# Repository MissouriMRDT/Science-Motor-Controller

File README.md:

# ScienceMotorController_Hardware
Hardware files for the Science Motor Controller (Science MOCO) board <br/>
The entire science system runs off of the 12V 40A auxillary buck from Powerboard. 
Science MOCO disctributes power to the rest of the science system (heater board and science sensors) in addition to driving brushed DC motors, servos, and solenoids.

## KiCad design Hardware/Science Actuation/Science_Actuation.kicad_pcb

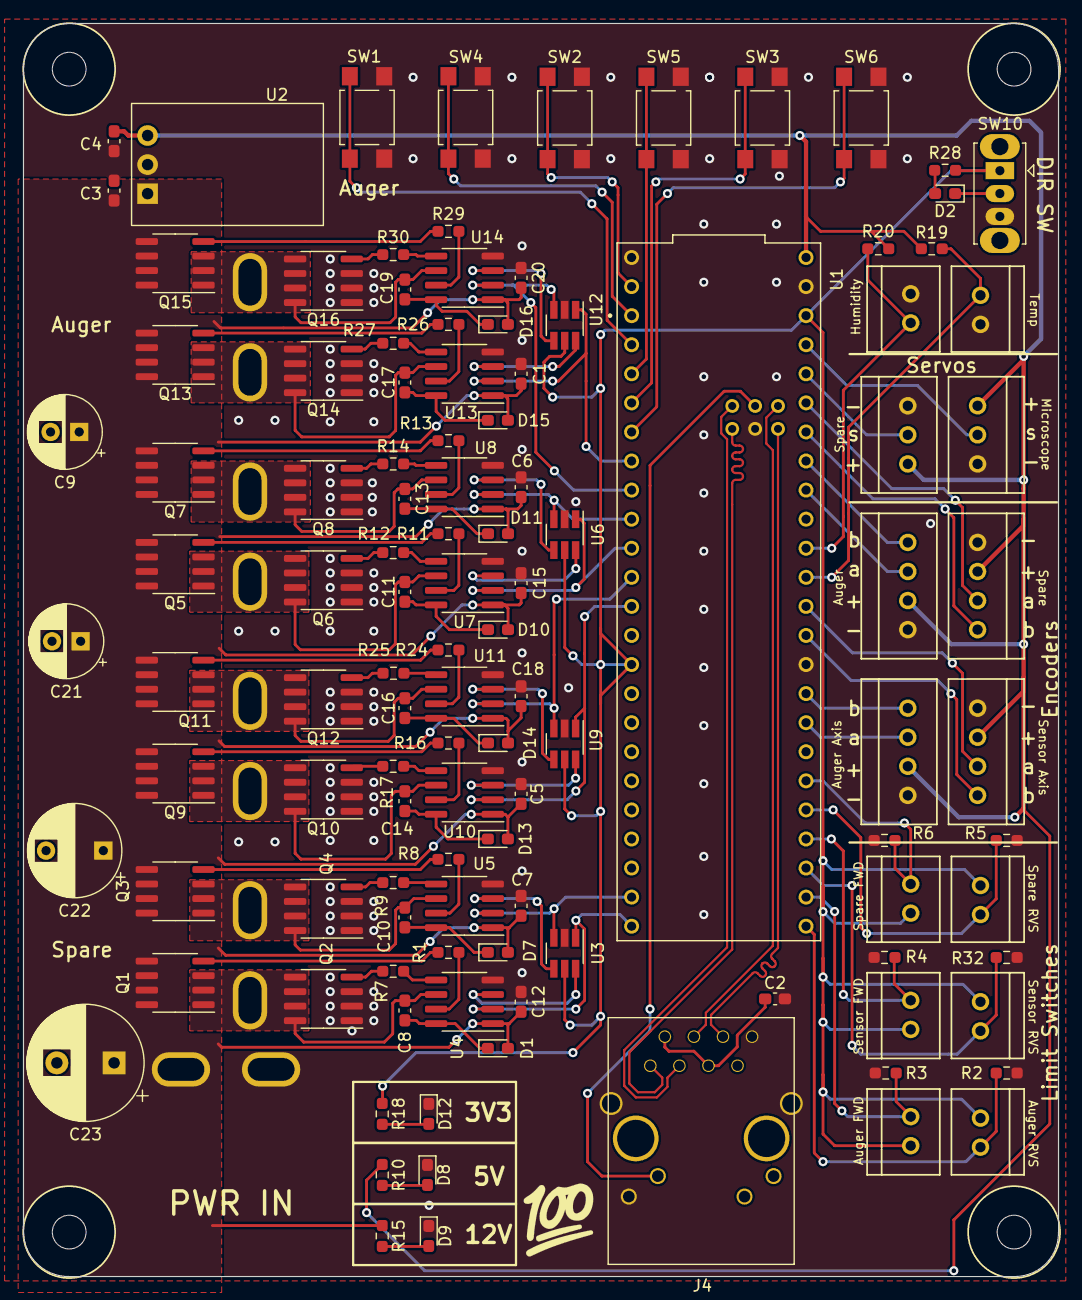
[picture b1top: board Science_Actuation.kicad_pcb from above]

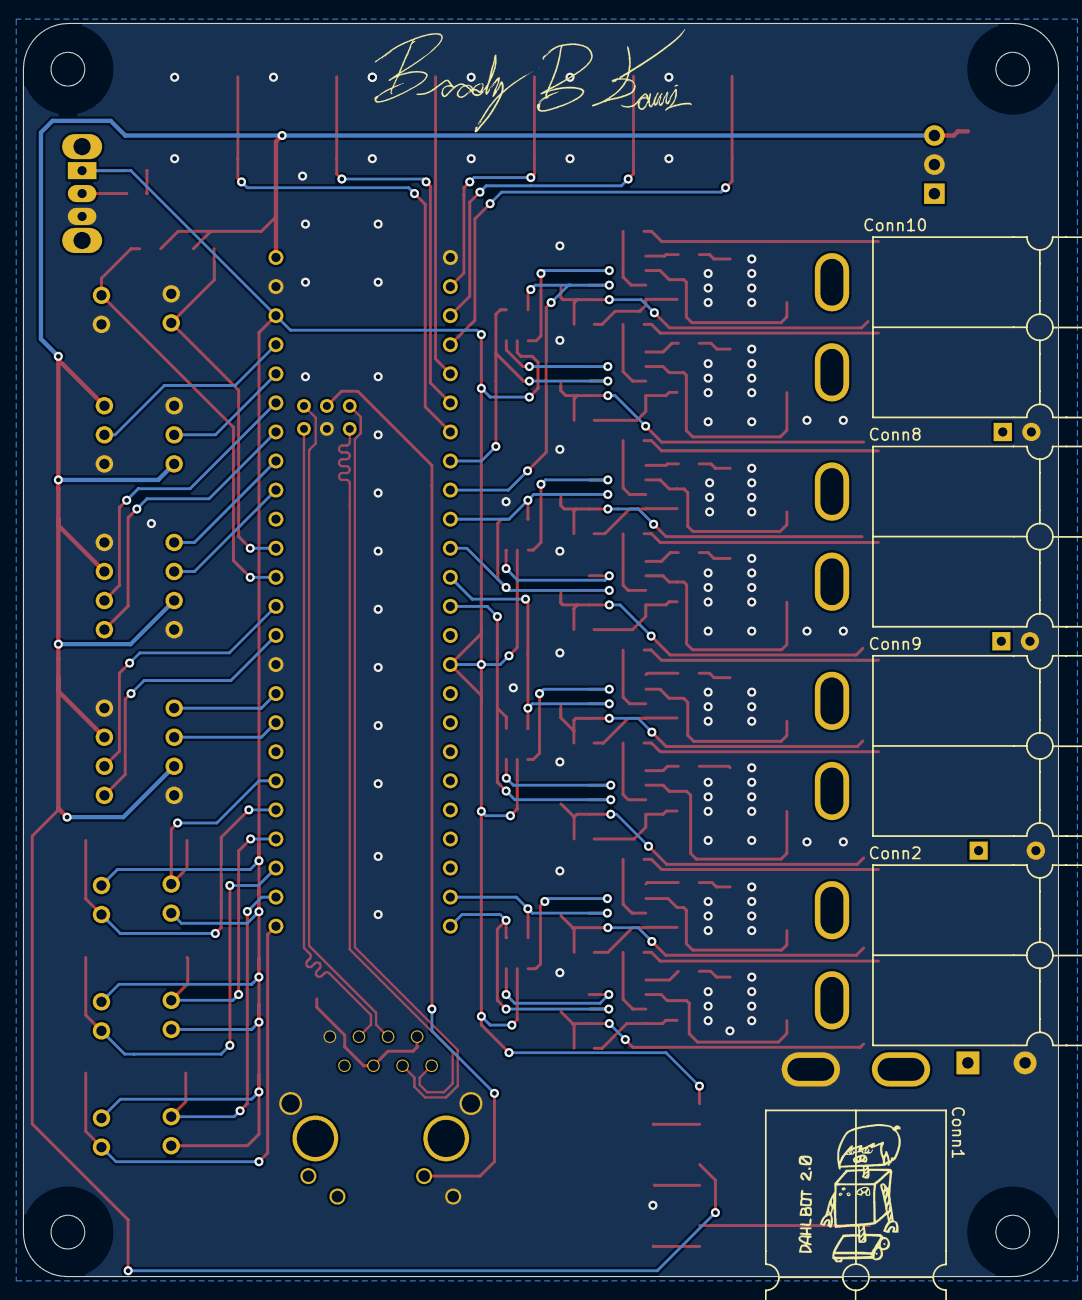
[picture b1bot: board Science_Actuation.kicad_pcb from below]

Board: 2 copper layers, 90.4 x 109.5 mm, 124 parts (5 on the bottom side), 103 nets.

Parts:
C1, C3, C4, C5, C6, C7, C12, C15, C18, C20: 10uF; C_0603_1608Metric_Pad1.08x0.95mm_HandSolder
C2: 0.1uF; C_0603_1608Metric_Pad1.08x0.95mm_HandSolder
C8, C10, C11, C13, C14, C16, C17, C19: 1uF; C_0603_1608Metric_Pad1.08x0.95mm_HandSolder
C9: 100uF; CP_Radial_D6.3mm_P2.50mm
C21: 220uF; CP_Radial_D6.3mm_P2.50mm
C22: 330uF; CP_Radial_D8.0mm_P5.00mm
C23: 470uF; CP_Radial_D10.0mm_P5.00mm
Conn1, Conn2, Conn8, Conn9, Conn10: AndersonPP; Square_Anderson_2_H_Side_By_Side
Conn3, Conn4, Conn5, Conn6, Conn7, Conn11, Conn12, Conn13: Molex_SL_02; MOLEX_SL_02_Vertical
D1, D7, D10, D11, D13, D14, D15, D16: SD0603S04; D_0603_1608Metric_Pad1.05x0.95mm_HandSolder
D2: Blue; LED_0603_1608Metric_Pad1.05x0.95mm_HandSolder
D8, D9, D12: Green; LED_0603_1608Metric_Pad1.05x0.95mm_HandSolder
H1, H2, H3, H4: MountingHole; 4_40_Hole_Corner
J4: RJ45_LED_Shielded; RJ45_Teensy
Q1, Q2, Q3, Q4, Q5, Q6, Q7, Q8, Q9, Q10, Q11, Q12, Q13, Q14, Q15, Q16: Si4156DY; SOIC-8_3.9x4.9mm_P1.27mm
QuadEncode1, QuadEncode2, QuadEncode3, QuadEncode4: Molex_SL_04; MOLEX_SL_04_Vertical
R1, R7, R8, R9, R11, R12, R13, R14, R16, R17, R24, R25, R26, R27, R29, R30: 100; R_0603_1608Metric_Pad0.98x0.95mm_HandSolder
R2, R3, R4, R5, R6, R32: 4700; R_0603_1608Metric_Pad0.98x0.95mm_HandSolder
R10: 560; R_0603_1608Metric_Pad0.98x0.95mm_HandSolder
R15: 2.2k; R_0603_1608Metric_Pad0.98x0.95mm_HandSolder
R18: 300; R_0603_1608Metric_Pad0.98x0.95mm_HandSolder
R19: 25; R_0603_1608Metric_Pad0.98x0.95mm_HandSolder
R20: 50k; R_0603_1608Metric_Pad0.98x0.95mm_HandSolder
R28: 30; R_0603_1608Metric_Pad0.98x0.95mm_HandSolder
SW1, SW2, SW3, SW4, SW5, SW6: SW_Push; SW_SPST_TL3305A
SW10: SW_SPDT; SW_Slide_1P2T_CK_OS102011MS2Q
Servo1, Servo2: Molex_SL_03; MOLEX_SL_03_Vertical
U1: Teensy4.1_DEV-16771; Teensy_4_1_Ethernet
U2: OKI-78SR-5_1.5-W36H-C; Converter_DCDC_Murata_OKI-78SR_Horizontal
U3, U6, U9, U12: 74LVC2G04; SOT-23-6_Handsoldering
U4, U5, U7, U8, U10, U11, U13, U14: IRS2308; SOIC-8_3.9x4.9mm_P1.27mm

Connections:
+3V3: Conn3.1, Conn4.1, Conn5.1, Conn6.1, Conn7.1, Conn11.1, R18.1, R28.1, SW10.1 (A), U1.3.3V_1 (3.3V), U1.3.3V_2 (3.3V), U3.5 (VCC), U6.5 (VCC), U9.5 (VCC), U12.5 (VCC)
+5V: C4.1, QuadEncode1.2, QuadEncode2.2, QuadEncode3.2, QuadEncode4.2, R10.1, R19.1, R20.1, Servo1.1, Servo2.1, U1.VIN, U2.3 (OUT)
+12V: C1.1, C3.1, C5.1, C6.1, C7.1, C9.1, C12.1, C15.1, C18.1, C20.1, C21.1, C22.1, C23.1, Conn1.2 (V+Log), D1.2 (A), D7.2 (A), D10.2 (A), D11.2 (A), D13.2 (A), D14.2 (A), D15.2 (A), D16.2 (A), Q1.5 (D), Q1.6 (D), Q1.7 (D), Q1.8 (D), Q3.5 (D), Q3.6 (D), Q3.7 (D), Q3.8 (D), Q5.5 (D), Q5.6 (D), Q5.7 (D), Q5.8 (D), Q7.5 (D), Q7.6 (D), Q7.7 (D), Q7.8 (D), Q9.5 (D), Q9.6 (D), Q9.7 (D), Q9.8 (D), Q11.5 (D), Q11.6 (D), Q11.7 (D), Q11.8 (D), Q13.5 (D), Q13.6 (D), Q13.7 (D), Q13.8 (D), Q15.5 (D), Q15.6 (D), Q15.7 (D), Q15.8 (D), R15.1, U2.1 (IN), U4.1 (VCC), U5.1 (VCC), U7.1 (VCC), U8.1 (VCC), U10.1 (VCC), U11.1 (VCC), U13.1 (VCC), U14.1 (VCC)
/M1+: C8.2, Conn2.1 (GND), Q1.1 (S), Q1.2 (S), Q1.3 (S), Q2.5 (D), Q2.6 (D), Q2.7 (D), Q2.8 (D), U4.6 (VS)
/M1-: C10.2, Conn2.2 (V+Log), Q3.1 (S), Q3.2 (S), Q3.3 (S), Q4.5 (D), Q4.6 (D), Q4.7 (D), Q4.8 (D), U5.6 (VS)
/M2+: C11.2, Conn8.1 (GND), Q5.1 (S), Q5.2 (S), Q5.3 (S), Q6.5 (D), Q6.6 (D), Q6.7 (D), Q6.8 (D), U7.6 (VS)
/M2-: C13.2, Conn8.2 (V+Log), Q7.1 (S), Q7.2 (S), Q7.3 (S), Q8.5 (D), Q8.6 (D), Q8.7 (D), Q8.8 (D), U8.6 (VS)
/M3+: C14.2, Conn9.1 (GND), Q9.1 (S), Q9.2 (S), Q9.3 (S), Q10.5 (D), Q10.6 (D), Q10.7 (D), Q10.8 (D), U10.6 (VS)
/M3-: C16.2, Conn9.2 (V+Log), Q11.1 (S), Q11.2 (S), Q11.3 (S), Q12.5 (D), Q12.6 (D), Q12.7 (D), Q12.8 (D), U11.6 (VS)
/M4+: C17.2, Conn10.1 (GND), Q13.1 (S), Q13.2 (S), Q13.3 (S), Q14.5 (D), Q14.6 (D), Q14.7 (D), Q14.8 (D), U13.6 (VS)
/M4-: C19.2, Conn10.2 (V+Log), Q15.1 (S), Q15.2 (S), Q15.3 (S), Q16.5 (D), Q16.6 (D), Q16.7 (D), Q16.8 (D), U14.6 (VS)
DIR_SW: D2.1 (K), SW10.2 (B)
Encoder_1a: QuadEncode4.3, U1.40 (A16)
Encoder_1b: QuadEncode4.4, U1.41 (A17)
Encoder_2a: QuadEncode1.3, U1.18 (A4)
Encoder_2b: QuadEncode1.4, U1.19 (A5)
Encoder_3a: QuadEncode2.3, U1.21 (A7)
Encoder_3b: QuadEncode2.4, U1.20 (A6)
Encoder_4a: QuadEncode3.3, U1.14 (A0)
Encoder_4b: QuadEncode3.4, U1.13 (SCK)
GND: C1.2, C2.1, C3.2, C4.2, C5.2, C6.2, C7.2, C9.2, C12.2, C15.2, C18.2, C20.2, C21.2, C22.2, C23.2, Conn1.1 (GND), Conn12.2, Conn13.2, D8.1 (K), D9.1 (K), D12.1 (K), J4.8, J4.9, J4.SH, Q2.1 (S), Q2.2 (S), Q2.3 (S), Q4.1 (S), Q4.2 (S), Q4.3 (S), Q6.1 (S), Q6.2 (S), Q6.3 (S), Q8.1 (S), Q8.2 (S), Q8.3 (S), Q10.1 (S), Q10.2 (S), Q10.3 (S), Q12.1 (S), Q12.2 (S), Q12.3 (S), Q14.1 (S), Q14.2 (S), Q14.3 (S), Q16.1 (S), Q16.2 (S), Q16.3 (S), QuadEncode1.1, QuadEncode2.1, QuadEncode3.1, QuadEncode4.1, R2.1, R3.1, R4.1, R5.1, R6.1, R32.1, SW1.2, SW2.2, SW3.2, SW4.2, SW5.2, SW6.2, SW10.3 (C), Servo1.3, Servo2.3, U1.GND1 (GND), U1.GND2 (GND), U1.GND3 (GND), U1.GND5 (GND), U2.2 (GND), U3.2 (GND), U4.4 (COM), U5.4 (COM), U6.2 (GND), U7.4 (COM), U8.4 (COM), U9.2 (GND), U10.4 (COM), U11.4 (COM), U12.2 (GND), U13.4 (COM), U14.4 (COM)
Humidity: Conn13.1, R20.2, U1.16 (A2)
LED: J4.10, U1.LED
LimitSwitch1: Conn3.2, R2.2, U1.33 (MCLK2)
LimitSwitch2: Conn4.2, R3.2, U1.34 (RX8)
LimitSwitch3: Conn5.2, R4.2, U1.36 (CS2)
LimitSwitch4: Conn6.2, R5.2, U1.37 (CS3)
LimitSwitch5: Conn7.2, R6.2, U1.38 (A14)
LimitSwitch6: Conn11.2, R32.2, U1.35 (TX8)
MOCO1_FWD: U1.32 (OUT1B), U3.1, U4.2 (HIN)
MOCO1_RVS: U1.31 (CTX3), U3.3, U5.2 (HIN)
MOCO2_FWD: U1.9 (OUT1C), U6.1, U7.2 (HIN)
MOCO2_RVS: U1.8 (TX2), U6.3, U8.2 (HIN)
MOCO3_FWD: U1.11 (MOSI), U9.1, U10.2 (HIN)
MOCO3_RVS: U1.10 (CS1), U9.3, U11.2 (HIN)
MOCO4_FWD: U1.6 (OUT1D), U12.1, U13.2 (HIN)
MOCO4_RVS: U1.7 (RX2), U12.3, U14.2 (HIN)
unnamed: C2.2, J4.2, J4.5
unnamed: C8.1, D1.1 (K), U4.8 (VB)
unnamed: D2.2 (A), R28.2
unnamed: C10.1, D7.1 (K), U5.8 (VB)
unnamed: D8.2 (A), R10.2
unnamed: D9.2 (A), R15.2
unnamed: C11.1, D10.1 (K), U7.8 (VB)
unnamed: C13.1, D11.1 (K), U8.8 (VB)
unnamed: D12.2 (A), R18.2
unnamed: C14.1, D13.1 (K), U10.8 (VB)
unnamed: C16.1, D14.1 (K), U11.8 (VB)
unnamed: C17.1, D15.1 (K), U13.8 (VB)
unnamed: C19.1, D16.1 (K), U14.8 (VB)
unnamed: Q1.4 (G), R1.2
unnamed: Q2.4 (G), R7.2
unnamed: Q3.4 (G), R8.2
unnamed: Q4.4 (G), R9.2
unnamed: Q5.4 (G), R11.2
unnamed: Q6.4 (G), R12.2
unnamed: Q7.4 (G), R13.2
unnamed: Q8.4 (G), R14.2
unnamed: Q9.4 (G), R16.2
unnamed: Q10.4 (G), R17.2
unnamed: Q11.4 (G), R24.2
unnamed: Q12.4 (G), R25.2
unnamed: Q13.4 (G), R26.2
unnamed: Q14.4 (G), R27.2
unnamed: Q15.4 (G), R29.2
unnamed: Q16.4 (G), R30.2
unnamed: R1.1, U4.7 (HO)
unnamed: U3.6, U4.3 (LIN)
unnamed: R7.1, U4.5 (LO)
unnamed: R8.1, U5.7 (HO)
unnamed: U3.4, U5.3 (LIN)
unnamed: R9.1, U5.5 (LO)
unnamed: R11.1, U7.7 (HO)
unnamed: U6.6, U7.3 (LIN)
unnamed: R12.1, U7.5 (LO)
unnamed: R13.1, U8.7 (HO)
unnamed: U6.4, U8.3 (LIN)
unnamed: R14.1, U8.5 (LO)
unnamed: R16.1, U10.7 (HO)
unnamed: U9.6, U10.3 (LIN)
unnamed: R17.1, U10.5 (LO)
unnamed: R24.1, U11.7 (HO)
unnamed: U9.4, U11.3 (LIN)
unnamed: R25.1, U11.5 (LO)
unnamed: R26.1, U13.7 (HO)
unnamed: U12.6, U13.3 (LIN)
unnamed: R27.1, U13.5 (LO)
unnamed: R29.1, U14.7 (HO)
unnamed: U12.4, U14.3 (LIN)
unnamed: R30.1, U14.5 (LO)
R+: J4.4, U1.R+
R-: J4.6, U1.R-
SW1: SW1.1, U1.2 (OUT2)
SW2: SW2.1, U1.0 (RX1)
SW3: SW3.1, U1.4 (BCLK2)
SW4: SW4.1, U1.1 (TX1)
SW5: SW5.1, U1.3 (LRCLK2)
SW6: SW6.1, U1.5 (IN2)
Servo_1: Servo2.2, U1.22 (A8)
Servo_2: Servo1.2, U1.23 (A9)
T+: J4.1, U1.T+
T-: J4.3, U1.T-
Temp: Conn12.1, R19.2, U1.15 (A1)

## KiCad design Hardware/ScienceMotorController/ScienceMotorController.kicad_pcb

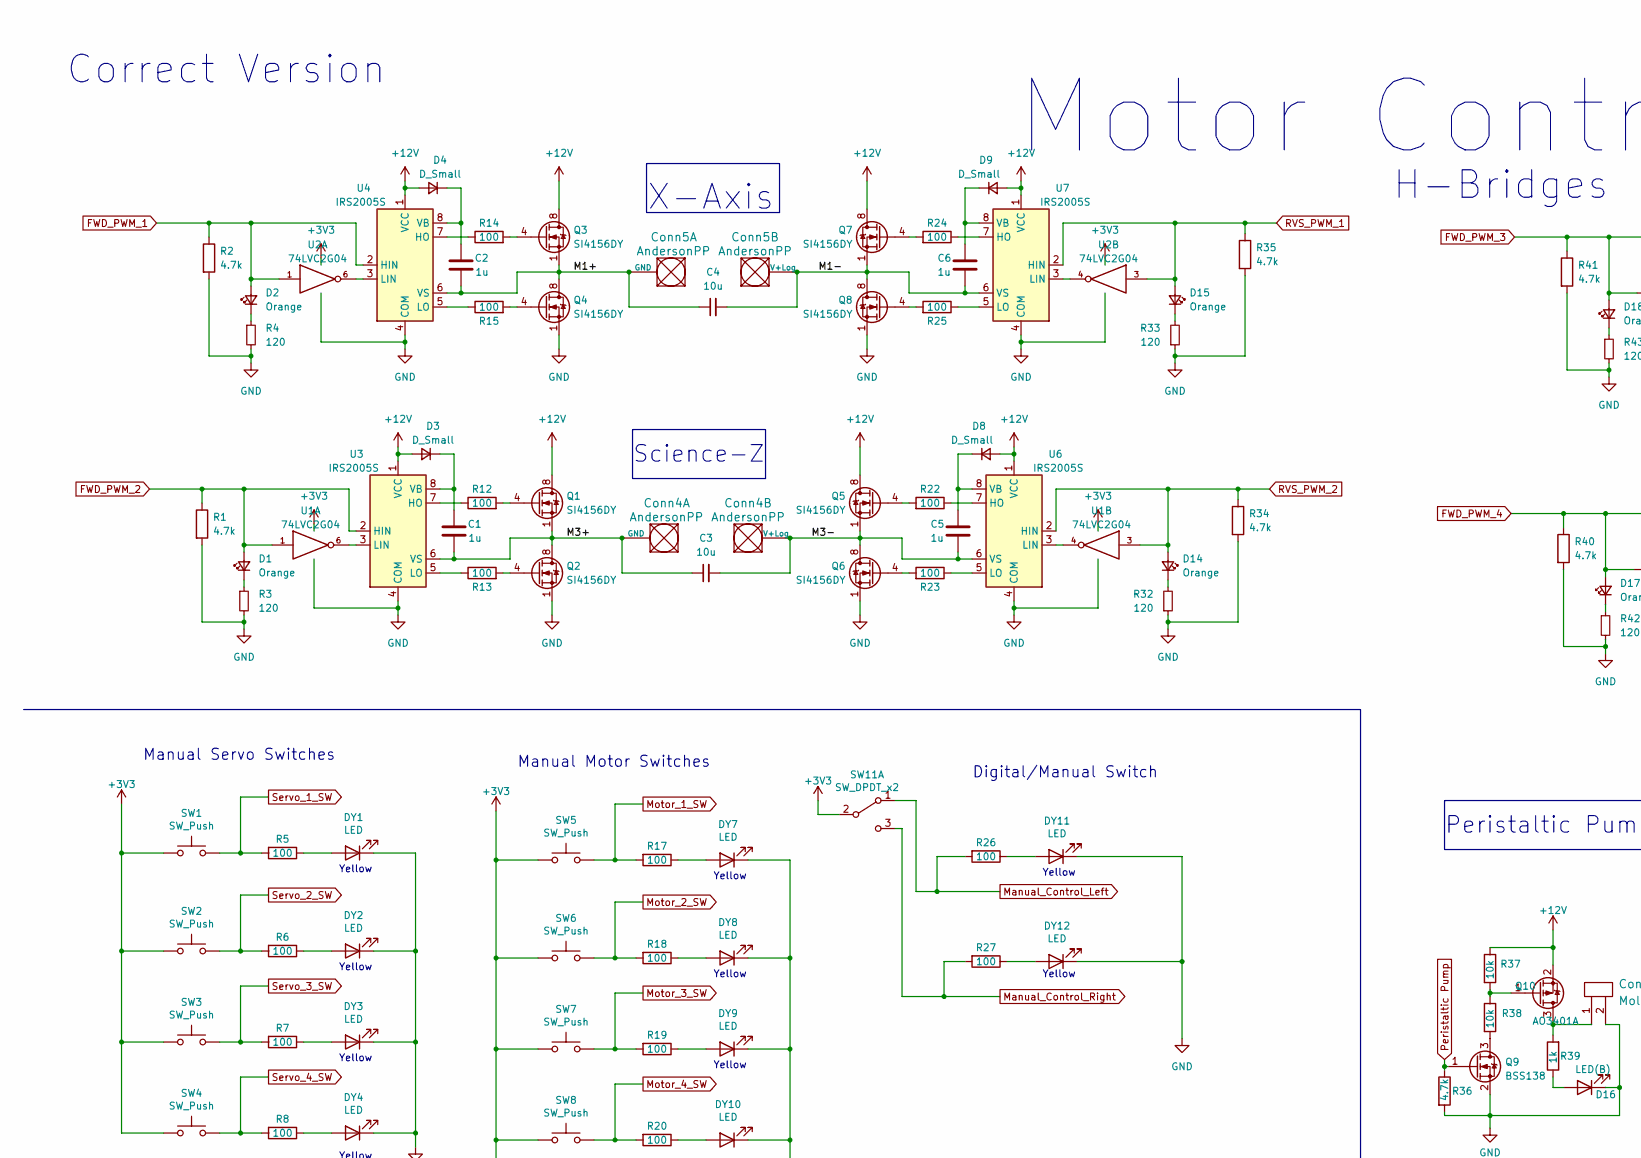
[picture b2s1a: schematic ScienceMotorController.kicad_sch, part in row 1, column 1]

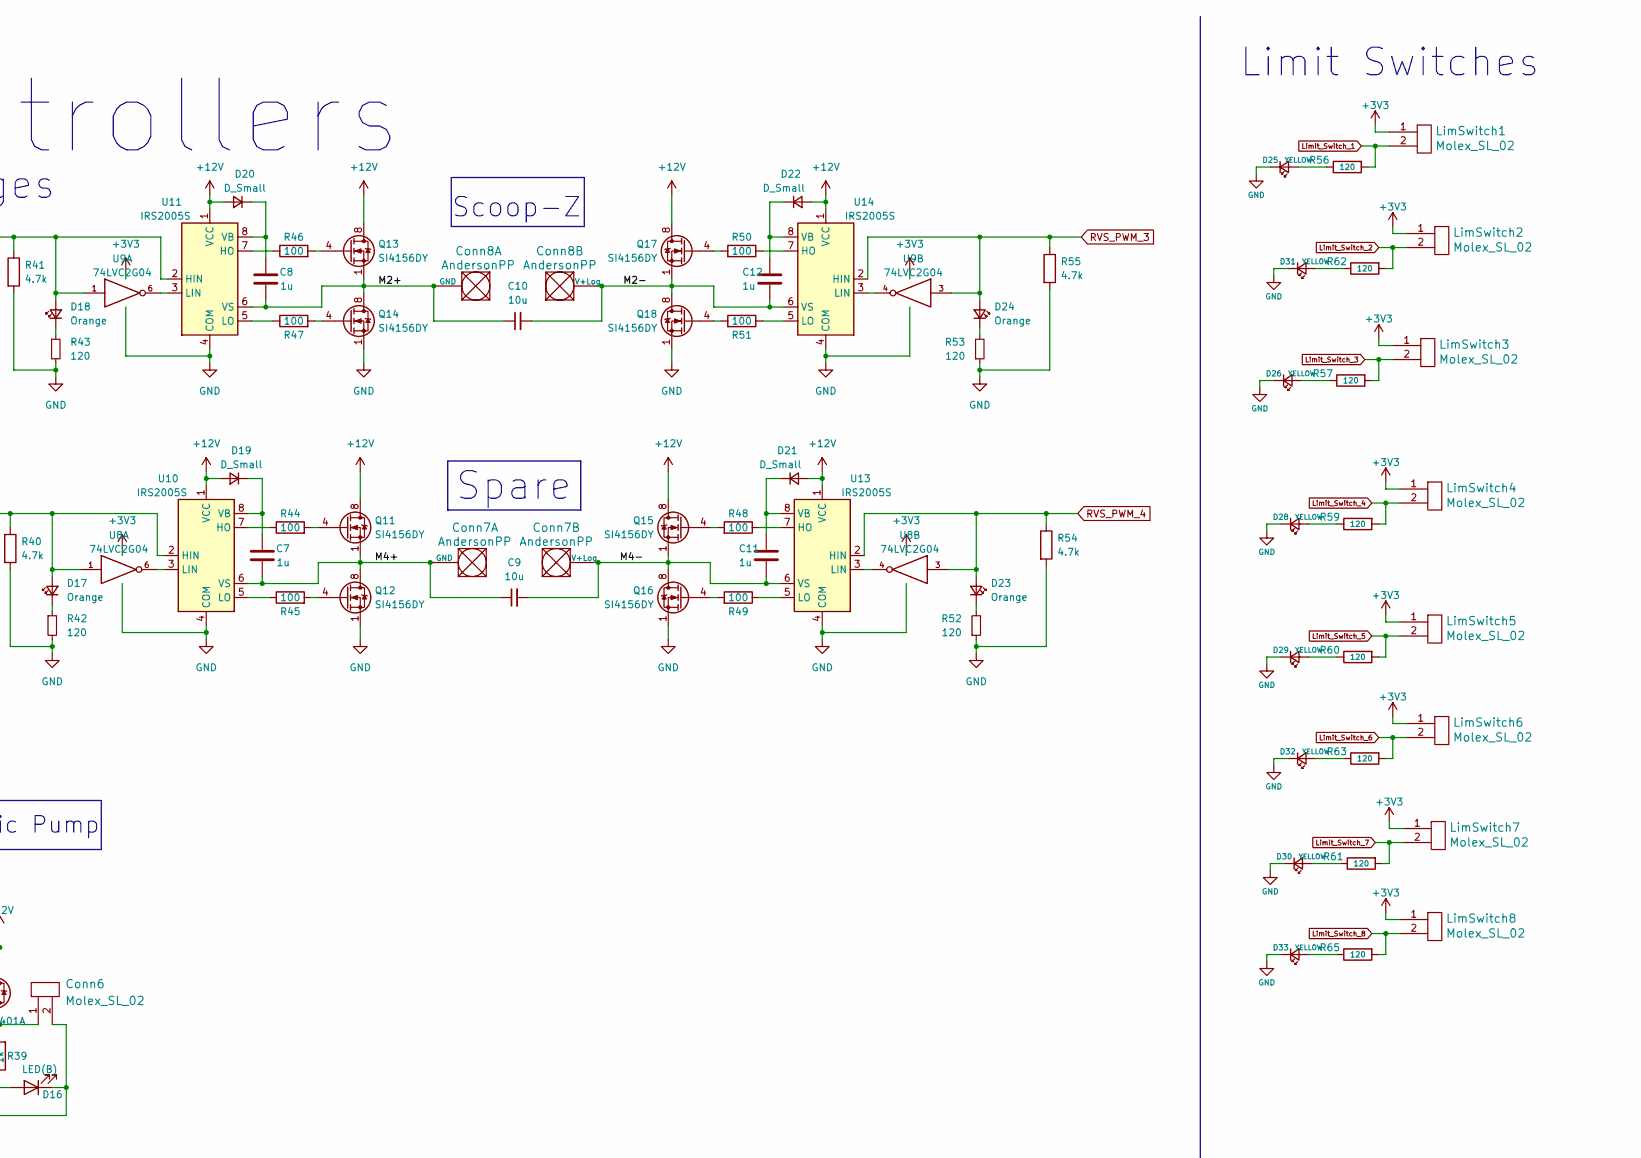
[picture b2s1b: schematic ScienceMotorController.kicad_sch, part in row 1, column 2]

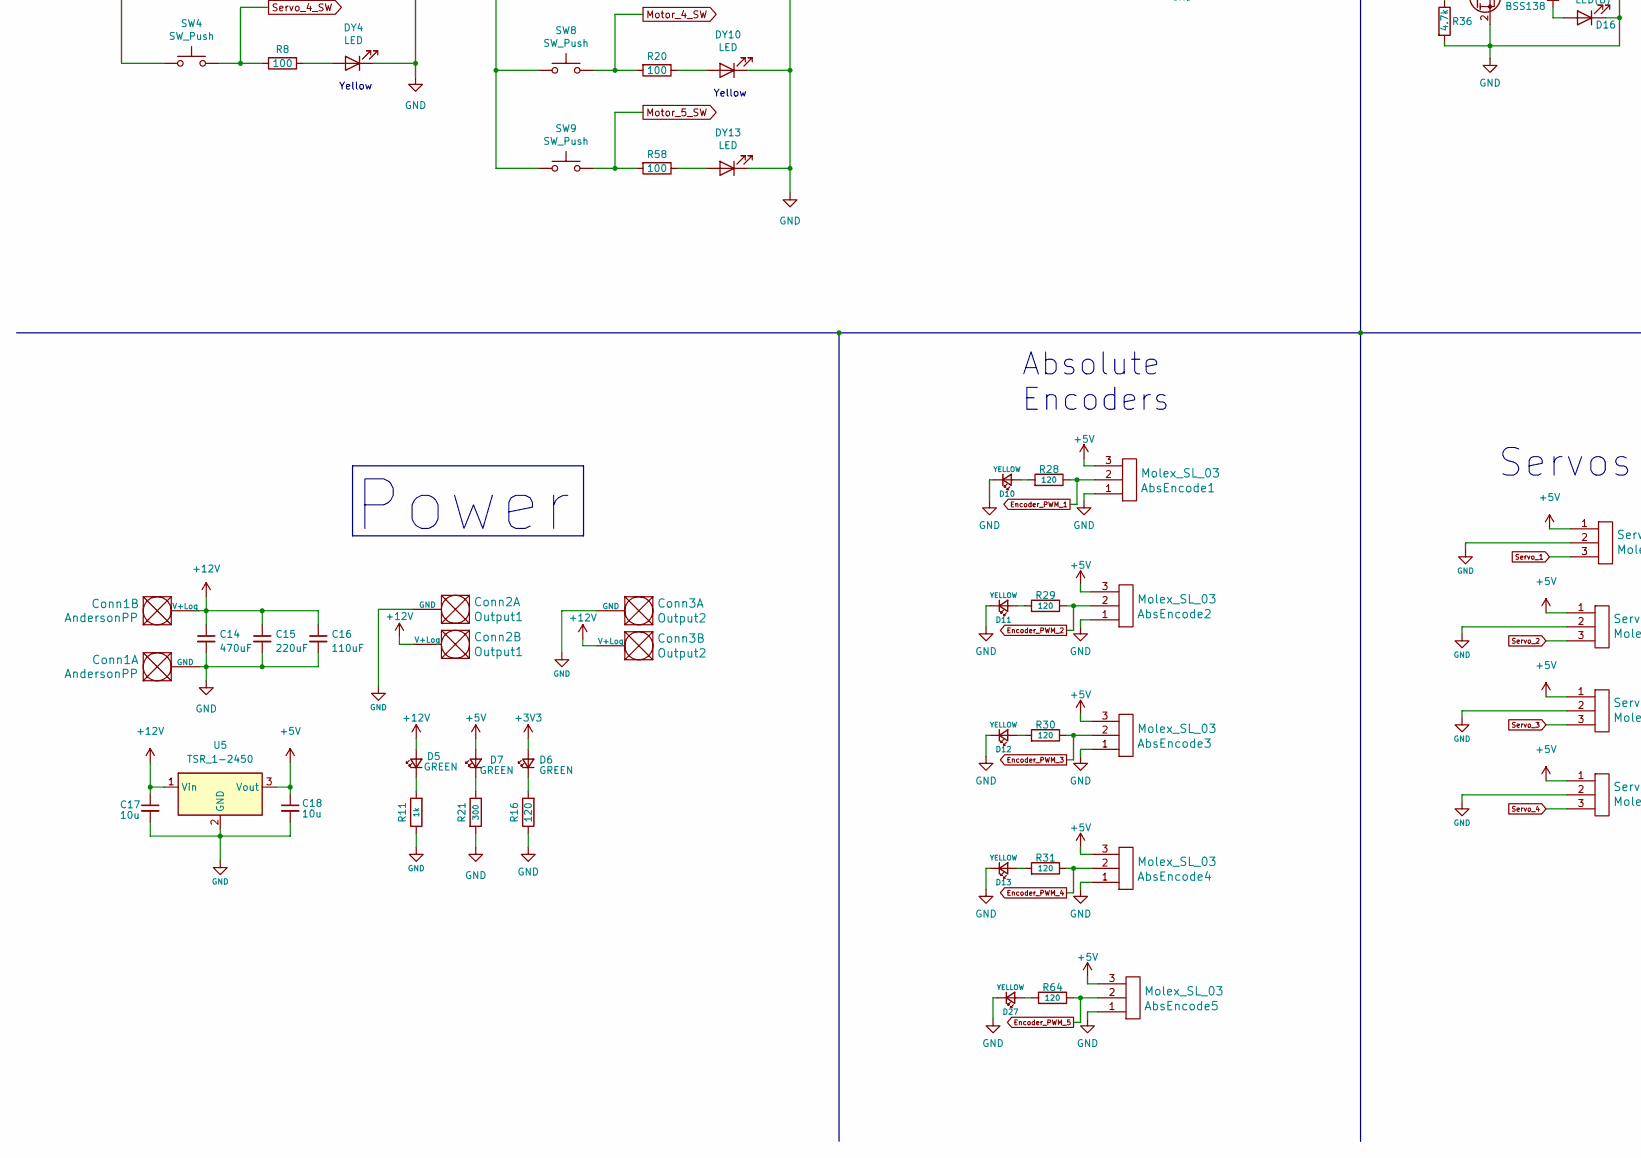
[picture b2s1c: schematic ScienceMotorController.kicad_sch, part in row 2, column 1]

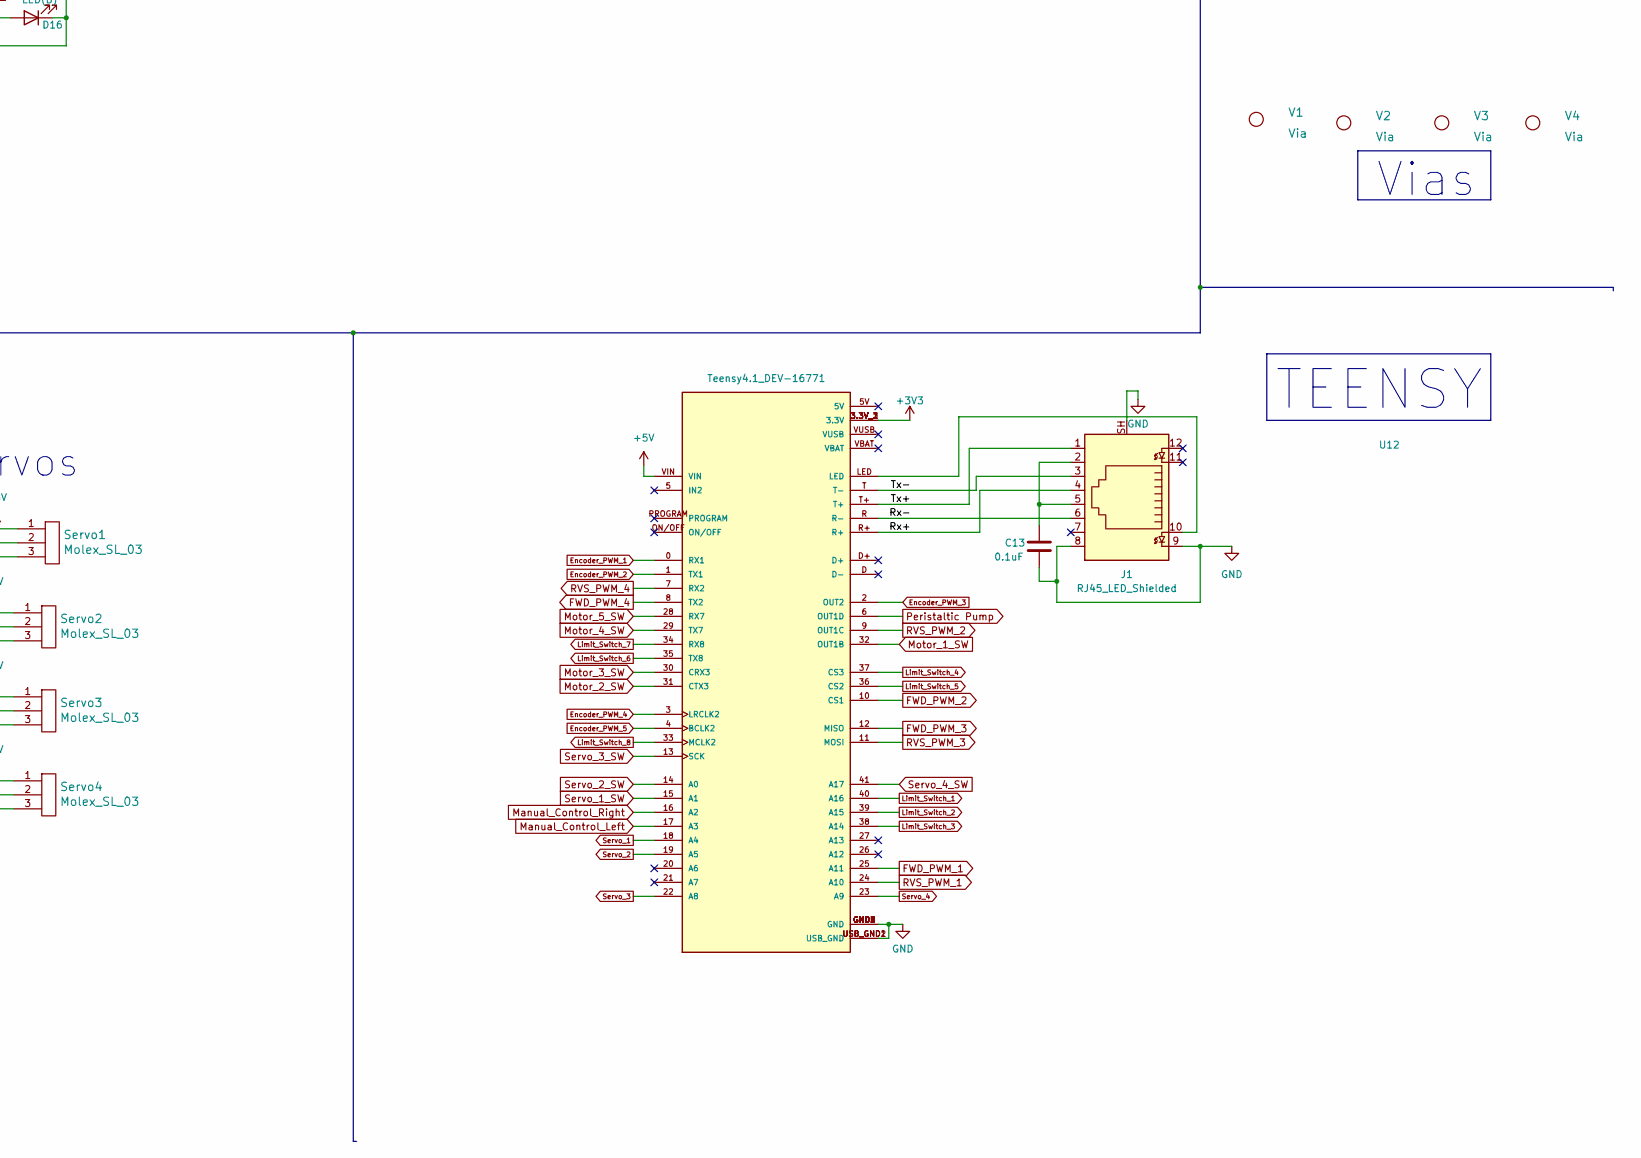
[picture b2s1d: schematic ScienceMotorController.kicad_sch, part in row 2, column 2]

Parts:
AbsEncode1, AbsEncode2, AbsEncode3, AbsEncode4, AbsEncode5: Molex_SL_03; MOLEX_SL_03_Vertical
C1, C2, C5, C6, C7, C8, C11, C12: 1u; C_0603_1608Metric
C3, C4, C9, C10, C17, C18: 10u; C_0603_1608Metric
C13: 0.1uF; C_0603_1608Metric_Pad1.08x0.95mm_HandSolder
C14: 470uF; CP_Radial_D6.3mm_P2.50mm
C15: 220uF; CP_Radial_D6.3mm_P2.50mm
C16: 110uF; CP_Radial_D6.3mm_P2.50mm
Conn1: AndersonPP; Square_Anderson_2_H_Stacked_PV
Conn2: Output1; Square_Anderson_2_H_Stacked_PV
Conn3: Output2; Square_Anderson_2_H_Stacked_PV
Conn4, Conn5, Conn7, Conn8: AndersonPP; Square_Anderson_2_H_Side_By_Side
Conn6: Molex_SL_02; MOLEX_SL_02_Vertical
D1, D2, D14, D15, D17, D18, D23, D24: Orange; LED_0603_1608Metric_Pad1.05x0.95mm_HandSolder
D3, D4, D8, D9, D19, D20, D21, D22: D_Small; LED_0603_1608Metric_Pad1.05x0.95mm_HandSolder
D5, D6, D7: GREEN; LED_0603_1608Metric_Pad1.05x0.95mm_HandSolder
D10, D11, D12, D13, D25, D26, D27, D28, D29, D30, D31, D32, D33: YELLOW; LED_0603_1608Metric_Pad1.05x0.95mm_HandSolder
D16: LED(B); LED_0603_1608Metric_Pad1.05x0.95mm_HandSolder
DY1, DY2, DY3, DY4, DY7, DY8, DY9, DY10, DY11, DY12, DY13: LED; LED_0603_1608Metric_Pad1.05x0.95mm_HandSolder
J1: RJ45_LED_Shielded; RJ45_Teensy
LimSwitch1, LimSwitch2, LimSwitch3, LimSwitch4, LimSwitch5, LimSwitch6, LimSwitch7, LimSwitch8: Molex_SL_02; MOLEX_SL_02_Vertical
Q1, Q2, Q3, Q4, Q5, Q6, Q7, Q8, Q11, Q12, Q13, Q14, Q15, Q16, Q17, Q18: SI4156DY; SOIC-8_3.9x4.9mm_P1.27mm
Q9: BSS138; SOT-23
Q10: AO3401A; SOT-23
R1, R2, R34, R35, R36, R40, R41, R54, R55: 4.7k; R_0603_1608Metric_Pad0.98x0.95mm_HandSolder
R3, R4, R16, R28, R29, R30, R31, R32, R33, R42, R43, R52, R53, R56, R57, R59, R60, R61, R62, R63, R64, R65: 120; R_0603_1608Metric_Pad0.98x0.95mm_HandSolder
R5, R6, R7, R8, R12, R13, R14, R15, R17, R18, R19, R20, R22, R23, R24, R25, R26, R27, R44, R45, R46, R47, R48, R49, R50, R51, R58: 100; R_0603_1608Metric_Pad0.98x0.95mm_HandSolder
R11, R39: 1k; R_0603_1608Metric_Pad0.98x0.95mm_HandSolder
R21: 300; R_0603_1608Metric_Pad0.98x0.95mm_HandSolder
R37, R38: 10k; R_0603_1608Metric_Pad0.98x0.95mm_HandSolder
SW1, SW2, SW3, SW4, SW5, SW6, SW7, SW8, SW9: SW_Push; SW_SPST_TL3305A
SW11: SW_DPDT_x2; SW_Slide_1P2T_CK_OS102011MS2Q
Servo1, Servo2, Servo3, Servo4: Molex_SL_03; MOLEX_SL_03_Vertical
U1, U2, U8, U9: 74LVC2G04; SOT-23-6_Handsoldering
U3, U4, U6, U7, U10, U11, U13, U14: IRS2005S; SOIC-8_3.9x4.9mm_P1.27mm
U5: TSR_1-2450; Converter_DCDC_TRACO_TSR-1_THT
U12: Teensy4.1_DEV-16771; Teensy_4_1_Ethernet; PARTREV 4.1
V1, V2, V3, V4: Via; 4_40_Hole_Corner

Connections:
+3V3: D6.2 (A), LimSwitch1.1, LimSwitch2.1, LimSwitch3.1, LimSwitch4.1, LimSwitch5.1, LimSwitch6.1, LimSwitch7.1, LimSwitch8.1, SW1.2, SW2.1, SW3.1, SW4.1, SW5.2, SW6.1, SW7.1, SW8.1, SW9.1, SW11.2 (B), U1.5 (VCC), U2.5 (VCC), U8.5 (VCC), U9.5 (VCC), U12.3.3V_1 (3.3V), U12.3.3V_2 (3.3V), U12.3.3V_3 (3.3V)
+5V: AbsEncode1.3, AbsEncode2.3, AbsEncode3.3, AbsEncode4.3, AbsEncode5.3, C18.1, D7.2 (A), Servo1.1, Servo2.1, Servo3.1, Servo4.1, U5.3 (Vout), U12.VIN
+12V: C14.1, C15.1, C16.1, C17.1, Conn1.2 (V+Log), Conn2.2 (V+Log), Conn3.2 (V+Log), D3.2 (A), D4.2 (A), D5.2 (A), D8.2 (A), D9.2 (A), D19.2 (A), D20.2 (A), D21.2 (A), D22.2 (A), Q1.5 (D), Q1.6 (D), Q1.7 (D), Q1.8 (D), Q3.5 (D), Q3.6 (D), Q3.7 (D), Q3.8 (D), Q5.5 (D), Q5.6 (D), Q5.7 (D), Q5.8 (D), Q7.5 (D), Q7.6 (D), Q7.7 (D), Q7.8 (D), Q10.2 (S), Q11.5 (D), Q11.6 (D), Q11.7 (D), Q11.8 (D), Q13.5 (D), Q13.6 (D), Q13.7 (D), Q13.8 (D), Q15.5 (D), Q15.6 (D), Q15.7 (D), Q15.8 (D), Q17.5 (D), Q17.6 (D), Q17.7 (D), Q17.8 (D), R37.1, U3.1 (VCC), U4.1 (VCC), U5.1 (Vin), U6.1 (VCC), U7.1 (VCC), U10.1 (VCC), U11.1 (VCC), U13.1 (VCC), U14.1 (VCC)
/M1+: C2.2, C4.1, Conn5.1 (GND), Q3.1 (S), Q3.2 (S), Q3.3 (S), Q4.5 (D), Q4.6 (D), Q4.7 (D), Q4.8 (D), U4.6 (VS)
/M1-: C4.2, C6.2, Conn5.2 (V+Log), Q7.1 (S), Q7.2 (S), Q7.3 (S), Q8.5 (D), Q8.6 (D), Q8.7 (D), Q8.8 (D), U7.6 (VS)
/M2+: C8.2, C10.1, Conn8.1 (GND), Q13.1 (S), Q13.2 (S), Q13.3 (S), Q14.5 (D), Q14.6 (D), Q14.7 (D), Q14.8 (D), U11.6 (VS)
/M2-: C10.2, C12.2, Conn8.2 (V+Log), Q17.1 (S), Q17.2 (S), Q17.3 (S), Q18.5 (D), Q18.6 (D), Q18.7 (D), Q18.8 (D), U14.6 (VS)
/M3+: C1.2, C3.1, Conn4.1 (GND), Q1.1 (S), Q1.2 (S), Q1.3 (S), Q2.5 (D), Q2.6 (D), Q2.7 (D), Q2.8 (D), U3.6 (VS)
/M3-: C3.2, C5.2, Conn4.2 (V+Log), Q5.1 (S), Q5.2 (S), Q5.3 (S), Q6.5 (D), Q6.6 (D), Q6.7 (D), Q6.8 (D), U6.6 (VS)
/M4+: C7.2, C9.1, Conn7.1 (GND), Q11.1 (S), Q11.2 (S), Q11.3 (S), Q12.5 (D), Q12.6 (D), Q12.7 (D), Q12.8 (D), U10.6 (VS)
/M4-: C9.2, C11.2, Conn7.2 (V+Log), Q15.1 (S), Q15.2 (S), Q15.3 (S), Q16.5 (D), Q16.6 (D), Q16.7 (D), Q16.8 (D), U13.6 (VS)
/Rx+: J1.4, U12.R+
/Rx-: J1.6, U12.R (R-), U12.R-
/Tx+: J1.1, U12.T+
/Tx-: J1.3, U12.T (T-), U12.T-
Encoder_PWM_1: AbsEncode1.2, R28.1, U12.0 (RX1)
Encoder_PWM_2: AbsEncode2.2, R29.1, U12.1 (TX1)
Encoder_PWM_3: AbsEncode3.2, R30.1, U12.2 (OUT2)
Encoder_PWM_4: AbsEncode4.2, R31.1, U12.3 (LRCLK2)
Encoder_PWM_5: AbsEncode5.2, R64.1, U12.4 (BCLK2)
FWD_PWM_1: D2.2 (A), R2.1, U2.1, U4.2 (HIN), U12.25 (A11)
FWD_PWM_2: D1.2 (A), R1.1, U1.1, U3.2 (HIN), U12.10 (CS1)
FWD_PWM_3: D18.2 (A), R41.1, U9.1, U11.2 (HIN), U12.12 (MISO)
FWD_PWM_4: D17.2 (A), R40.1, U8.1, U10.2 (HIN), U12.8 (TX2)
GND: AbsEncode1.1, AbsEncode2.1, AbsEncode3.1, AbsEncode4.1, AbsEncode5.1, C13.2, C14.2, C15.2, C16.2, C17.2, C18.2, Conn1.1 (GND), Conn2.1 (GND), Conn3.1 (GND), Conn6.2, D10.1 (K), D11.1 (K), D12.1 (K), D13.1 (K), D16.1 (K), D25.1 (K), D26.1 (K), D27.1 (K), D28.1 (K), D29.1 (K), D30.1 (K), D31.1 (K), D32.1 (K), D33.1 (K), DY1.1 (K), DY2.1 (K), DY3.1 (K), DY4.1 (K), DY7.1 (K), DY8.1 (K), DY9.1 (K), DY10.1 (K), DY11.1 (K), DY12.1 (K), DY13.1 (K), J1.8, J1.9, J1.SH, Q2.1 (S), Q2.2 (S), Q2.3 (S), Q4.1 (S), Q4.2 (S), Q4.3 (S), Q6.1 (S), Q6.2 (S), Q6.3 (S), Q8.1 (S), Q8.2 (S), Q8.3 (S), Q9.2 (S), Q12.1 (S), Q12.2 (S), Q12.3 (S), Q14.1 (S), Q14.2 (S), Q14.3 (S), Q16.1 (S), Q16.2 (S), Q16.3 (S), Q18.1 (S), Q18.2 (S), Q18.3 (S), R1.2, R2.2, R3.2, R4.2, R11.1, R16.1, R21.2, R32.1, R33.1, R34.2, R35.2, R36.2, R40.2, R41.2, R42.2, R43.2, R52.1, R53.1, R54.2, R55.2, Servo1.2, Servo2.2, Servo3.2, Servo4.2, U1.2 (GND), U2.2 (GND), U3.4 (COM), U4.4 (COM), U5.2 (GND), U6.4 (COM), U7.4 (COM), U8.2 (GND), U9.2 (GND), U10.4 (COM), U11.4 (COM), U12.GND1 (GND), U12.GND2 (GND), U12.GND3 (GND), U12.GND4 (GND), U12.GND5 (GND), U12.USB_GND1 (USB_GND), U12.USB_GND2 (USB_GND), U13.4 (COM), U14.4 (COM)
Limit_Switch_1: LimSwitch1.2, R56.2, U12.40 (A16)
Limit_Switch_2: LimSwitch2.2, R62.2, U12.39 (A15)
Limit_Switch_3: LimSwitch3.2, R57.2, U12.38 (A14)
Limit_Switch_4: LimSwitch4.2, R59.2, U12.37 (CS3)
Limit_Switch_5: LimSwitch5.2, R60.2, U12.36 (CS2)
Limit_Switch_6: LimSwitch6.2, R63.2, U12.35 (TX8)
Limit_Switch_7: LimSwitch7.2, R61.2, U12.34 (RX8)
Limit_Switch_8: LimSwitch8.2, R65.2, U12.33 (MCLK2)
Manual_Control_Left: R26.2, SW11.1 (A), U12.17 (A3)
Manual_Control_Right: R27.2, SW11.3 (C), U12.16 (A2)
Motor_1_SW: R17.2, SW5.1, U12.32 (OUT1B)
Motor_2_SW: R18.2, SW6.2, U12.31 (CTX3)
Motor_3_SW: R19.2, SW7.2, U12.30 (CRX3)
Motor_4_SW: R20.2, SW8.2, U12.29 (TX7)
Motor_5_SW: R58.2, SW9.2, U12.28 (RX7)
unnamed: C1.1, D3.1 (K), U3.8 (VB)
unnamed: C2.1, D4.1 (K), U4.8 (VB)
unnamed: C5.1, D8.1 (K), U6.8 (VB)
unnamed: C6.1, D9.1 (K), U7.8 (VB)
unnamed: C7.1, D19.1 (K), U10.8 (VB)
unnamed: C8.1, D20.1 (K), U11.8 (VB)
unnamed: C11.1, D21.1 (K), U13.8 (VB)
unnamed: C12.1, D22.1 (K), U14.8 (VB)
unnamed: C13.1, J1.2, J1.5
unnamed: Conn6.1, Q10.3 (D), R39.2
unnamed: D1.1 (K), R3.1
unnamed: D2.1 (K), R4.1
unnamed: D5.1 (K), R11.2
unnamed: D6.1 (K), R16.2
unnamed: D7.1 (K), R21.1
unnamed: D10.2 (A), R28.2
unnamed: D11.2 (A), R29.2
unnamed: D12.2 (A), R30.2
unnamed: D13.2 (A), R31.2
unnamed: D14.1 (K), R32.2
unnamed: D15.1 (K), R33.2
unnamed: D16.2 (A), R39.1
unnamed: D17.1 (K), R42.1
unnamed: D18.1 (K), R43.1
unnamed: D23.1 (K), R52.2
unnamed: D24.1 (K), R53.2
unnamed: D25.2 (A), R56.1
unnamed: D26.2 (A), R57.1
unnamed: D27.2 (A), R64.2
unnamed: D28.2 (A), R59.1
unnamed: D29.2 (A), R60.1
unnamed: D30.2 (A), R61.1
unnamed: D31.2 (A), R62.1
unnamed: D32.2 (A), R63.1
unnamed: D33.2 (A), R65.1
unnamed: DY1.2 (A), R5.1
unnamed: DY2.2 (A), R6.1
unnamed: DY3.2 (A), R7.1
unnamed: DY4.2 (A), R8.1
unnamed: DY7.2 (A), R17.1
unnamed: DY8.2 (A), R18.1
unnamed: DY9.2 (A), R19.1
unnamed: DY10.2 (A), R20.1
unnamed: DY11.2 (A), R26.1
unnamed: DY12.2 (A), R27.1
unnamed: DY13.2 (A), R58.1
unnamed: J1.10, U12.LED
unnamed: Q1.4 (G), R12.2
unnamed: Q2.4 (G), R13.2
unnamed: Q3.4 (G), R14.2
unnamed: Q4.4 (G), R15.2
unnamed: Q5.4 (G), R22.2
unnamed: Q6.4 (G), R23.2
unnamed: Q7.4 (G), R24.2
unnamed: Q8.4 (G), R25.2
unnamed: Q9.3 (D), R38.2
unnamed: Q10.1 (G), R37.2, R38.1
unnamed: Q11.4 (G), R44.2
unnamed: Q12.4 (G), R45.2
unnamed: Q13.4 (G), R46.2
unnamed: Q14.4 (G), R47.2
unnamed: Q15.4 (G), R48.2
unnamed: Q16.4 (G), R49.2
unnamed: Q17.4 (G), R50.2
unnamed: Q18.4 (G), R51.2
unnamed: R12.1, U3.7 (HO)
unnamed: R13.1, U3.5 (LO)
unnamed: R14.1, U4.7 (HO)
unnamed: R15.1, U4.5 (LO)
unnamed: R22.1, U6.7 (HO)
unnamed: R23.1, U6.5 (LO)
unnamed: R24.1, U7.7 (HO)
unnamed: R25.1, U7.5 (LO)
unnamed: R44.1, U10.7 (HO)
unnamed: R45.1, U10.5 (LO)
unnamed: R46.1, U11.7 (HO)
unnamed: R47.1, U11.5 (LO)
unnamed: R48.1, U13.7 (HO)
unnamed: R49.1, U13.5 (LO)
unnamed: R50.1, U14.7 (HO)
unnamed: R51.1, U14.5 (LO)
unnamed: U1.4, U6.3 (LIN)
unnamed: U1.6, U3.3 (LIN)
unnamed: U2.4, U7.3 (LIN)
unnamed: U2.6, U4.3 (LIN)
unnamed: U8.6, U10.3 (LIN)
unnamed: U9.6, U11.3 (LIN)
unnamed: U8.4, U13.3 (LIN)
unnamed: U9.4, U14.3 (LIN)
Peristaltic Pump: Q9.1 (G), R36.1, U12.6 (OUT1D)
RVS_PWM_1: D15.2 (A), R35.1, U2.3, U7.2 (HIN), U12.24 (A10)
RVS_PWM_2: D14.2 (A), R34.1, U1.3, U6.2 (HIN), U12.9 (OUT1C)
RVS_PWM_3: D24.2 (A), R55.1, U9.3, U12.11 (MOSI), U14.2 (HIN)
RVS_PWM_4: D23.2 (A), R54.1, U8.3, U12.7 (RX2), U13.2 (HIN)
Servo_1: Servo1.3, U12.18 (A4)
Servo_1_SW: R5.2, SW1.1, U12.15 (A1)
Servo_2: Servo2.3, U12.19 (A5)
Servo_2_SW: R6.2, SW2.2, U12.14 (A0)
Servo_3: Servo3.3, U12.22 (A8)
Servo_3_SW: R7.2, SW3.2, U12.13 (SCK)
Servo_4: Servo4.3, U12.23 (A9)
Servo_4_SW: R8.2, SW4.2, U12.41 (A17)

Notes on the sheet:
Scoop-Z
Yellow
X-Axis
Peristaltic Pump
Absolute Encoders
Digital/Manual Switch
H-Bridges
TEENSY
Manual Motor Switches
Correct Version
Motor Controllers
Limit Switches
Science-Z
Vias
Servos
Spare
Power
Manual Servo Switches

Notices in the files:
parts and their libraries:
Copyright 2016 Accelerated Designs. All rights reserved.
